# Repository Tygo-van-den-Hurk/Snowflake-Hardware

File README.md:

<br>
<div align="center">
  <!-- Colors:
    Dark Blue: #258DA8
    Light Blue: #50ABE2
    Dark Red: #C83434
    Light Red: #CE4785
 -->
  <picture>
    
  </picture>
  >
  <br><br>
  <b>Snowflake</b>
  <p>My first 100% self made keyboard.</p>
      <!--~###################################~-->
    <!--~####    Open issues and PRs    ####~-->
    <!--~###################################~-->
    <a href="https://github.com/Tygo-van-den-Hurk/Snowflake-Hardware/issues?q=is%3Aissue%20state%3Aopen%20label%3Afix">
      <picture>
        <source srcset="https://img.shields.io/github/issues/Tygo-van-den-Hurk/Snowflake-Hardware/fix?style=flat&labelColor=FFFFFF&color=50ABE2&logoColor=5E2751&label=Bug%20Reports" media="(prefers-color-scheme: light)" />
        
      </picture>
    </a>
    <a href="https://github.com/Tygo-van-den-Hurk/Snowflake-Hardware/issues?q=is%3Aissue%20state%3Aopen%20label%3Afeat">
      <picture>
        <source srcset="https://img.shields.io/github/issues/Tygo-van-den-Hurk/Snowflake-Hardware/feat?style=flat&labelColor=FFFFFF&color=50ABE2&logoColor=5E2751&label=Feature%20Requests" media="(prefers-color-scheme: light)" />
        
      </picture>
    </a>
    <a href="https://github.com/Tygo-van-den-Hurk/Snowflake-Hardware/blob/main/LICENSE">
      <picture>
        <source srcset="https://img.shields.io/github/license/Tygo-van-den-Hurk/Snowflake-Hardware?style=flat&labelColor=FFFFFF&color=50ABE2&logoColor=5E2751&label=Licence" media="(prefers-color-scheme: light)" />
        
      </picture>
    </a>
    <!-- NEW LINE --> <br>
    <a href="https://github.com/Tygo-van-den-Hurk/Snowflake-Hardware/stargazers">
      <picture>
        <source srcset="https://img.shields.io/github/stars/Tygo-van-den-Hurk/Snowflake-Hardware?style=flat&labelColor=FFFFFF&color=CE4785&label=Stars" media="(prefers-color-scheme: light)" />
        
      </picture>
    </a>
    <a href="https://github.com/Tygo-van-den-Hurk/Snowflake-Hardware/releases">
      <picture>
        <source srcset="https://img.shields.io/github/release/Tygo-van-den-Hurk/Snowflake-Hardware?style=flat&display_name=release&label=Release&labelColor=FFFFFF&color=CE4785" media="(prefers-color-scheme: light)" />
        
      </picture>
    </a>
  <!--~###################################~-->
  <!--~####      Repository CI/CD     ####~-->
  <!--~###################################~-->
  <a href="https://github.com/Tygo-van-den-Hurk/Snowflake-Hardware/actions/workflows/nix-github-actions.yml">
    <picture>
      <source srcset="https://img.shields.io/github/actions/workflow/status/Tygo-van-den-Hurk/Snowflake-Hardware/nix-github-actions.yml?style=flat&labelColor=FFFFFF&color=CE4785&logo=GitHub%20Actions&logoColor=000000&branch=main&event=push&label=CI" media="(prefers-color-scheme: light)" />
      
    </picture>
  </a>
  <a href="https://github.com/Tygo-van-den-Hurk/Snowflake-Hardware/actions/workflows/deploy-github-pages.yml">
    <picture>
      <source srcset="https://img.shields.io/github/actions/workflow/status/Tygo-van-den-Hurk/Snowflake-Hardware/deploy-github-pages.yml?style=flat&labelColor=FFFFFF&color=CE4785&logo=readthedocs&logoColor=000000&branch=main&event=push&label=Docs" media="(prefers-color-scheme: light)" />
      
    </picture>
  </a>
</div>
<br>

This repository is for the journey of me making my first keyboard: _Snowflake_.
I wanted a keyboard that works for me, I wanted something that I could take
with me anywhere and would work the way I designed it to do. This also was a
good excuse to learn about keyboards which is something I've wanted to do for
a while now.

## Software

Since every hardware iteration has different software configuration they've
been moved into their own repositories:

- v1: doesn't have firmware as the PCB had errors in it.
- v2: has [its own firmware repository][v2] for firmware.

## Credits

This code is written by, or using the help of:

- [@Narkoleptika][@nark] for providing the pro micro footprint and setting me
  up with a template.
- [@RajuBuddharaju][@raju] for helping me realize every part of this keyboard.
- [@Tygo-van-den-Hurk][@tygo] for finalizing the design.

To see how to start or develop see [CONTRIBUTING.md][contributing].

[@nark]: https://github.com/Narkoleptika
[@raju]: https://github.com/RajuBuddharaju
[@tygo]: https://redirects.tygo.van.den.hurk.dev/github/personal/
[contributing]: ./CONTRIBUTING.md
[v2]: https://github.com/Tygo-van-den-Hurk/Snowflake-v2-Firmware

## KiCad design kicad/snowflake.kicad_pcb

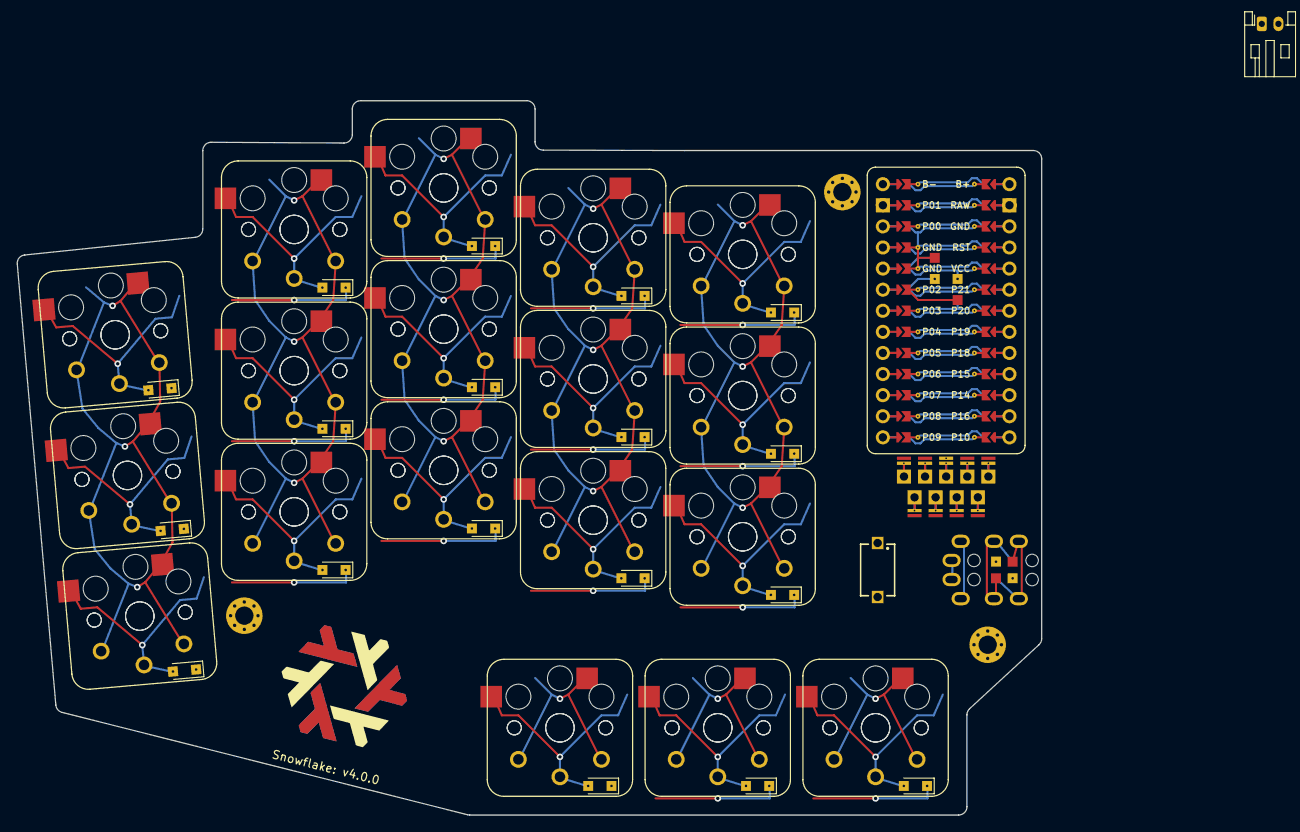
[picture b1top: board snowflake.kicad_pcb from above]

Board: 2 copper layers, 123.3 x 86.0 mm, 64 parts (0 on the bottom side), 36 nets.

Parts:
D1, D2, D3, D4, D5, D6, D7, D8, D9, D10, D11, D12, D13, D14, D15, D16, D17, D18: Nexperia_CFP3_SOD-123W
S1, S2, S3, S4, S5, S6, S7, S8, S9, S10, S11, S12, S13, S14, S15, S16, S17, S18, S19, S20, S21, S22, S23, S24, S25, S26, S27, S28, S29, S30, S31, S32, S33, S34, S35, S36: PG1350
TRRS1: TRRS-PJ-320A-dual
_1: JST_PH_S2B-PH-K_1x02_P2.00mm_Horizontal
_9, _10, _11: MountingHole_2.2mm_M2_Pad_Via
nice!nano1: nice!nano
threeWayJumper1, threeWayJumper2, threeWayJumper3, threeWayJumper4: Jumper; Jumper_1TH_2SMD

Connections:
B+: _1.1, nice!nano1.1
B-: _1.2, nice!nano1.124
D0: TRRS1.3, threeWayJumper3.3, threeWayJumper4.2
D1: TRRS1.4, threeWayJumper3.2, threeWayJumper4.3
GND: TRRS1.2, nice!nano1.3, nice!nano1.120, nice!nano1.121, threeWayJumper1.2
P02: nice!nano1.119, threeWayJumper2.2
P03: nice!nano1.118, threeWayJumper2.3
P08: D3.1, D6.1, D9.1, D12.1, D15.1, nice!nano1.113
P09: D2.1, D5.1, D8.1, D11.1, D14.1, nice!nano1.112
P10: D1.1, D4.1, D7.1, D10.1, D13.1, nice!nano1.13
P14: S1.1, S2.1, S3.1, S19.1, S20.1, S21.1, nice!nano1.11
P15: S4.1, S5.1, S6.1, S22.1, S23.1, S24.1, nice!nano1.10
P16: D16.1, D17.1, D18.1, nice!nano1.12
P18: S7.1, S8.1, S9.1, S16.1, S25.1, S26.1, S27.1, S34.1, nice!nano1.9
P19: S10.1, S11.1, S12.1, S17.1, S28.1, S29.1, S30.1, S35.1, nice!nano1.8
P20: S13.1, S14.1, S15.1, S18.1, S31.1, S32.1, S33.1, S36.1, nice!nano1.7
P21: nice!nano1.6, threeWayJumper1.1
VCC: TRRS1.1, nice!nano1.5, threeWayJumper1.3, threeWayJumper2.1
matrix_index_bottom: D10.2, S10.2, S28.2
matrix_index_home: D11.2, S11.2, S29.2
matrix_index_top: D12.2, S12.2, S30.2
matrix_inner_bottom: D13.2, S13.2, S31.2
matrix_inner_home: D14.2, S14.2, S32.2
matrix_inner_top: D15.2, S15.2, S33.2
matrix_middle_bottom: D7.2, S7.2, S25.2
matrix_middle_home: D8.2, S8.2, S26.2
matrix_middle_top: D9.2, S9.2, S27.2
matrix_pinky_bottom: D1.2, S1.2, S19.2
matrix_pinky_home: D2.2, S2.2, S20.2
matrix_pinky_top: D3.2, S3.2, S21.2
matrix_ring_bottom: D4.2, S4.2, S22.2
matrix_ring_home: D5.2, S5.2, S23.2
matrix_ring_top: D6.2, S6.2, S24.2
thumbfan_far_thumb: D18.2, S18.2, S36.2
thumbfan_home_thumb: D17.2, S17.2, S35.2
thumbfan_near_thumb: D16.2, S16.2, S34.2

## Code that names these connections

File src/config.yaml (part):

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outlines._board:
  pinky:
    $extends: outlines._finger_pcb.base
    $args: [&b matrix_pinky_bottom, &t matrix_pinky_top, *t, *b]
  ring:
    $extends: outlines._finger_pcb.base
    $args: [&b matrix_ring_bottom, &t matrix_ring_top, *t, *b]
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  what: polygon
  fillet: *board_fillet
  points:
    - ref: matrix_pinky_home
      shift: [direction_L * case_key_distance, direction_B * case_key_distance]
    - ref: matrix_pinky_bottom
      shift: [direction_L * case_key_distance, direction_B * case_key_distance]
    - ref: thumbfan_near_thumb
      shift: [direction_L * case_key_distance, direction_B * case_key_distance]
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
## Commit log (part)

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2025-05-25 Redesigned the keyboard fixing a lot of the issues
    So there were several issues with the keyboard I decided to address.
    Those being:
    - there was a short circuit between VCC and data. This is why any
    version before this one should not be considered. This was in relation
    to the TRRS connector that was invalidly configured.
    - removed the longly outer pinky key as I don't think it will serve any
2025-05-26 Updated the image to represent the new keyboard
    Updated the image of the keyboard to reflect the redesign.
2025-05-26 Wired the keyboard
    Wired the keyboard based on the previous changes.
2025-05-26 Formatted some files that weren't formatted
    Just ran nix fmt to format them
2025-05-26 Start to ignore tar files
    This is as these are archive files that can be easily produced, but also
    they are in binary format and thus not easy to track and update. Thus
    they are better left outside of the repository.
2025-06-16 Bump softprops/action-gh-release from 2.2.2 to 2.3.2
    Bumps [softprops/action-gh-release](https://github.com/softprops/action-gh-release) from 2.2.2 to 2.3.2.
    - [Release notes](https://github.com/softprops/action-gh-release/releases)
    - [Changelog](https://github.com/softprops/action-gh-release/blob/master/CHANGELOG.md)
    - [Commits](https://github.com/softprops/action-gh-release/compare/v2.2.2...v2.3.2)
    ---
    updated-dependencies:
2025-06-17 deps: Bump softprops/action-gh-release from 2.2.2 to 2.3.2 (#23)
    Bumps [softprops/action-gh-release](https://github.com/softprops/action-gh-release) from 2.2.2 to 2.3.2.
    - [Release notes](https://github.com/softprops/action-gh-release/releases)
    - [Changelog](https://github.com/softprops/action-gh-release/blob/master/CHANGELOG.md)
    - [Commits](https://github.com/softprops/action-gh-release/compare/v2.2.2...v2.3.2)
    ---
    updated-dependencies:
2025-06-26 fix: TRRS connector being to close to the edge
    some TRRS connectors with big husles would get stuck on the edge and would
    not be able to able to go in all the way. This commit resolves that issue.
    closes #24
2025-06-26 fix: TRRS connector being to close to the edge (#25)
    some TRRS connectors with big husles would get stuck on the edge and would
    not be able to able to go in all the way. This commit resolves that issue.
    closes #24
2025-07-07 feat!: added a 3 way jumpers
    So while building the firmware for version 2, I found that I could not
    easily build the firmware deterministically as a write to the EPROM is
    required the first time you flash the firmware. It would be nice to
    have a hardware option to decide what side it is. We solder anything
    into one of two possible configurations anyways, thus this does not
    make the PCB less flexible.
2025-07-07 feat!: added a 3 way jumpers (#28)
    So while building the firmware for version 2, I found that I could not
    easily build the firmware deterministically as a write to the EPROM is
    required the first time you flash the firmware. It would be nice to
    have a hardware option to decide what side it is. We solder anything
    into one of two possible configurations anyways, thus this does not
    make the PCB less flexible.
2025-07-07 fix: failing PR labeler
    See https://github.com/school-Tygo-van-den-Hurk/template/pull/37 and
    commit 6175bc1ce529fc846b296b38f3a209fa669cb07a on
    github.com:school-Tygo-van-den-Hurk#37
    Closes #29: "Fix failing PR labeler".
2025-07-07 fix: failing PR labeler (#30)
    See https://github.com/school-Tygo-van-den-Hurk/template/pull/37 and
    commit 6175bc1ce529fc846b296b38f3a209fa669cb07a on
    github.com:school-Tygo-van-den-Hurk#37
    Closes #29: "Fix failing PR labeler".
2025-07-07 feat: made the derivation output both halves of the case
    Before this only the left half was outputted. Now it renders the left half
    after which it mirrors it, and outputs that. Normally you could just find a
    website and make that flip it for you, now that is being done in nix.
    Closes #27: "Make STLs produce both case halves"
2025-07-08 fix: saw a single wire that was not wired up
    There was a missing connection between two keys the PCB would not have worked
    without this fix.
2025-07-08 deps: add 'admesh' program as a dependency
    This dependency is needed to check 3D object files, and repair them.
    It also comes with the feature that it can convert to different file
    types.
2025-07-08 feat: add multiple output types
    Now you get 5 output types. These being: binary-stl, ascii-stl, dxf, off, vrml.
2025-07-08 fix: derivation naming
    Almost all were named "pcb", when they were something else.
    Closes #34: "rename derivations to what they produce instead of all being PCB".
2025-07-08 docs: Removed software directory and flattened the hardware directory
    As discussed in #33, the software directory does not belong in this repostitory
    as this is the hardware repository.
    Further more I expanded the documentation to explain why we use points for the
    microcontroller for example, and how we use it.
    Closes #19: "Hardware documentation out of date.".
    Closes #20: "Explain why we created points in hardware README".
2025-07-09 feat: added guide
    This guide contains an overview of how to build the keyboard from scratch,
    even if it is a little more sparse then I'd have liked. The pictures for
    example are placeholders until I solder a new keyboard and have a chance
    to actually take pictures.
    Closes #31: "feat: add guide".
2025-07-09 fix: made deploy workflow trigger on image or style files
    Closes #22: "Changes in image should also trigger a redeploymrent of GitHub
    pages".
2025-07-09 fix: formatting release page
    Closes #15: "Fix formatting of links on release page".
2025-07-21 Bump actions/first-interaction from 1 to 2
    ---
    updated-dependencies:
    - dependency-name: actions/first-interaction
    dependency-version: '2'
    dependency-type: direct:production
    update-type: version-update:semver-major
2025-08-12 Bump actions/first-interaction from 1 to 3
    Bumps [actions/first-interaction](https://github.com/actions/first-interaction) from 1 to 3.
    - [Release notes](https://github.com/actions/first-interaction/releases)
    - [Commits](https://github.com/actions/first-interaction/compare/v1...v3)
    ---
    updated-dependencies:
    - dependency-name: actions/first-interaction
2025-08-12 Bump actions/checkout from 4 to 5
    Bumps [actions/checkout](https://github.com/actions/checkout) from 4 to 5.
    - [Release notes](https://github.com/actions/checkout/releases)
    - [Changelog](https://github.com/actions/checkout/blob/main/CHANGELOG.md)
    - [Commits](https://github.com/actions/checkout/compare/v4...v5)
    ---
    updated-dependencies:
2025-09-15 Bump softprops/action-gh-release from 2.3.2 to 2.3.3
    Bumps [softprops/action-gh-release](https://github.com/softprops/action-gh-release) from 2.3.2 to 2.3.3.
    - [Release notes](https://github.com/softprops/action-gh-release/releases)
    - [Changelog](https://github.com/softprops/action-gh-release/blob/master/CHANGELOG.md)
    - [Commits](https://github.com/softprops/action-gh-release/compare/v2.3.2...v2.3.3)
    ---
    updated-dependencies:
2025-09-15 deps: Bump softprops/action-gh-release from 2.3.2 to 2.3.3 (#43)
    Bumps
    [softprops/action-gh-release](https://github.com/softprops/action-gh-release)
    from 2.3.2 to 2.3.3.
    <details>
    <summary>Release notes</summary>
    <p><em>Sourced from <a
2025-09-15 Bump actions/upload-pages-artifact from 3 to 4
    Bumps [actions/upload-pages-artifact](https://github.com/actions/upload-pages-artifact) from 3 to 4.
    - [Release notes](https://github.com/actions/upload-pages-artifact/releases)
    - [Commits](https://github.com/actions/upload-pages-artifact/compare/v3...v4)
    ---
    updated-dependencies:
    - dependency-name: actions/upload-pages-artifact
2025-09-15 Bump actions/labeler from 5 to 6
    Bumps [actions/labeler](https://github.com/actions/labeler) from 5 to 6.
    - [Release notes](https://github.com/actions/labeler/releases)
    - [Commits](https://github.com/actions/labeler/compare/v5...v6)
    ---
    updated-dependencies:
    - dependency-name: actions/labeler
2025-10-06 Bump softprops/action-gh-release from 2.3.3 to 2.3.4
    Bumps [softprops/action-gh-release](https://github.com/softprops/action-gh-release) from 2.3.3 to 2.3.4.
    - [Release notes](https://github.com/softprops/action-gh-release/releases)
    - [Changelog](https://github.com/softprops/action-gh-release/blob/master/CHANGELOG.md)
    - [Commits](https://github.com/softprops/action-gh-release/compare/v2.3.3...v2.3.4)
    ---
    updated-dependencies:
2025-10-13 Bump softprops/action-gh-release from 2.3.3 to 2.4.1
    Bumps [softprops/action-gh-release](https://github.com/softprops/action-gh-release) from 2.3.3 to 2.4.1.
    - [Release notes](https://github.com/softprops/action-gh-release/releases)
    - [Changelog](https://github.com/softprops/action-gh-release/blob/master/CHANGELOG.md)
    - [Commits](https://github.com/softprops/action-gh-release/compare/v2.3.3...v2.4.1)
    ---
    updated-dependencies:
2025-10-24 chore(deps): Bump softprops/action-gh-release from 2.3.3 to 2.4.1 (#46)
    Bumps
    [softprops/action-gh-release](https://github.com/softprops/action-gh-release)
    from 2.3.3 to 2.4.1.
    <details>
    <summary>Release notes</summary>
    <p><em>Sourced from <a
2025-11-10 chore(deps): Bump softprops/action-gh-release from 2.4.1 to 2.4.2
    Bumps [softprops/action-gh-release](https://github.com/softprops/action-gh-release) from 2.4.1 to 2.4.2.
    - [Release notes](https://github.com/softprops/action-gh-release/releases)
    - [Changelog](https://github.com/softprops/action-gh-release/blob/master/CHANGELOG.md)
    - [Commits](https://github.com/softprops/action-gh-release/compare/v2.4.1...v2.4.2)
    ---
    updated-dependencies:
2026-02-25 chore: backup
    I am not done with these changes but am about to wipe my computer.
